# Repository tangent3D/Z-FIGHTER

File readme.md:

### Description
Z-FIGHTER is a Z80 hobby computer loosely based on [Grant Searle's CP/M on breadboard](http://searle.x10host.com/cpm/index.html "Grant Searle's CP/M on breadboard") project. As a fully assembled unit in its custom 3D-printed enclosure, Z-FIGHTER has a handheld-style form factor with front panel accessories intended for user-created software and games. Connected via serial to a computer or terminal, Z-FIGHTER can be used to enjoy a full CP/M 2.2 environment or Microsoft BASIC in ROM. Finally, a parallel port and external CPU control pins are provided to the user for hardware hacking and expansion.

### Specifications
- Z80 CPU @ 7.3728MHz
- CompactFlash interface for CP/M 2.2 operating system and file storage
- Z80 SIO/0 with dual 115200 bps RS-232 ports
- Jumper-selectable optional clock oscillator (X2) for SIO/0 port B (e.g.  614.4 KHz/64 for 9600 bps)
- Jumper-selectable RS-232 CTS flow control
- i8255 PPI-based parallel port reserved for front panel accessory daughterboard
- i8255 PPI-based user parallel port
- 512K ROM with external DIP-3 switches for manual ROM paging and ATF22V10C SPLD for memory map customization
- USB type-B power connector
- DS1233 supervisory circuit
- Optional jumpers to supply +5V to pin 9 on RS-232 ports (non-standard, for use at user's own risk)
- External CPU control header exposing #INT, #NMI, #WAIT, #RESET, system clock and SIO Ch. B clock signals

### Accessory board specifications
- 8x Cherry MX key switches
- ST7920 128x64 LCD module with software-controllable backlight
- Electromagnetic buzzer (CPU-controlled)

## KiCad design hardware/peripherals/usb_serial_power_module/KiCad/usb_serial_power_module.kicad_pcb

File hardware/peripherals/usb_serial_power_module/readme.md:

USB serial adapter with software-controllable pin 9 +5V. Not adherent to RS-232 standard. For use with Z-FIGHTER only.

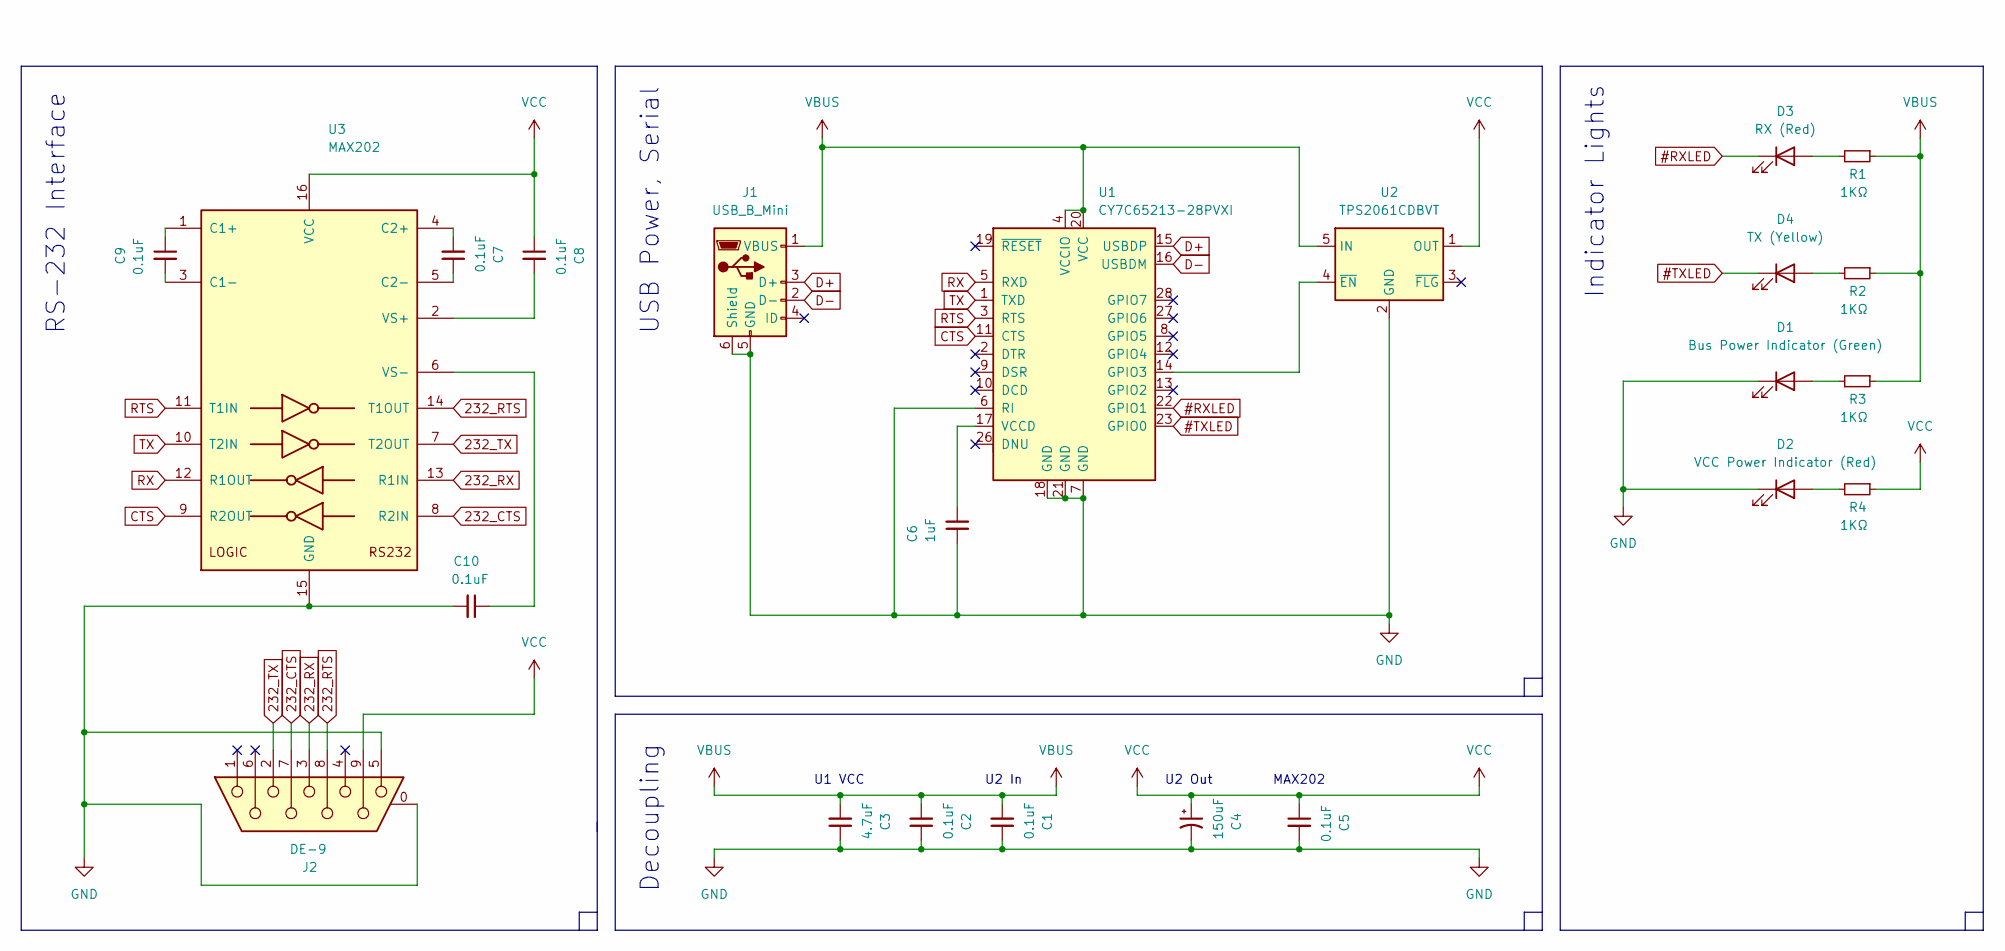
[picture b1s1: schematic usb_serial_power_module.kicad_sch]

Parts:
C1, C2, C5, C7, C8, C9, C10: 0.1uF; C_0805_2012Metric_Pad1.18x1.45mm_HandSolder
C3: 4.7uF; C_0805_2012Metric_Pad1.18x1.45mm_HandSolder
C4: 150uF; CP_EIA-6032-15_Kemet-U_Pad2.25x2.35mm_HandSolder
C6: 1uF; C_0805_2012Metric_Pad1.18x1.45mm_HandSolder
D1: Bus Power Indicator (Green); LED_0805_2012Metric_Pad1.15x1.40mm_HandSolder
D2: VCC Power Indicator (Red); LED_0805_2012Metric_Pad1.15x1.40mm_HandSolder
D3: RX (Red); LED_0805_2012Metric_Pad1.15x1.40mm_HandSolder
D4: TX (Yellow); LED_0805_2012Metric_Pad1.15x1.40mm_HandSolder
J1: USB_B_Mini; USB_Mini-B_Wuerth_65100516121_Horizontal
J2: DE-9; DSUB-9_Female_Horizontal_P2.77x2.84mm_EdgePinOffset7.70mm_H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
R1, R2, R3, R4: 1KΩ; R_0805_2012Metric_Pad1.20x1.40mm_HandSolder
U1: CY7C65213-28PVXI; SSOP-28_5.3x10.2mm_P0.65mm
U2: TPS2061CDBVT; SOT-23-5
U3: MAX202; SOIC-16_3.9x9.9mm_P1.27mm

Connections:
232_CTS: J2.7, U3.8 (R2IN)
232_RTS: J2.8, U3.14 (T1OUT)
232_RX: J2.3, U3.13 (R1IN)
232_TX: J2.2, U3.7 (T2OUT)
#RXLED: D3.1 (K), U1.22 (GPIO1)
#TXLED: D4.1 (K), U1.23 (GPIO0)
CTS: U1.11 (CTS), U3.9 (R2OUT)
D+: J1.3 (D+), U1.15 (USBDP)
D-: J1.2 (D-), U1.16 (USBDM)
GND: C1.1, C2.1, C3.1, C4.2, C5.2, C6.1, C10.2, D1.1 (K), D2.1 (K), J1.5 (GND), J1.6 (Shield), J2.0 (PAD), J2.5, U1.6 (RI), U1.7 (GND), U1.18 (GND), U1.21 (GND), U2.2 (GND), U3.15 (GND)
unnamed: C6.2, U1.17 (VCCD)
unnamed: C7.1, U3.5 (C2-)
unnamed: C7.2, U3.4 (C2+)
unnamed: C8.2, U3.2 (VS+)
unnamed: C9.1, U3.1 (C1+)
unnamed: C9.2, U3.3 (C1-)
unnamed: C10.1, U3.6 (VS-)
unnamed: D3.2 (A), R1.2
unnamed: D4.2 (A), R2.2
unnamed: D1.2 (A), R3.2
unnamed: D2.2 (A), R4.2
unnamed: U1.14 (GPIO3), U2.4 (~EN)
RTS: U1.3 (RTS), U3.11 (T1IN)
RX: U1.5 (RXD), U3.12 (R1OUT)
TX: U1.1 (TXD), U3.10 (T2IN)
VBUS: C1.2, C2.2, C3.2, J1.1 (VBUS), R1.1, R2.1, R3.1, U1.4 (VCCIO), U1.20 (VCC), U2.5 (IN)
VCC: C4.1, C5.1, C8.1, J2.9, R4.1, U2.1 (OUT), U3.16 (VCC)

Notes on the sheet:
Indicator Lights
Decoupling
RS-232 Interface
U1 VCC
U2 In
USB Power, Serial
MAX202
U2 Out

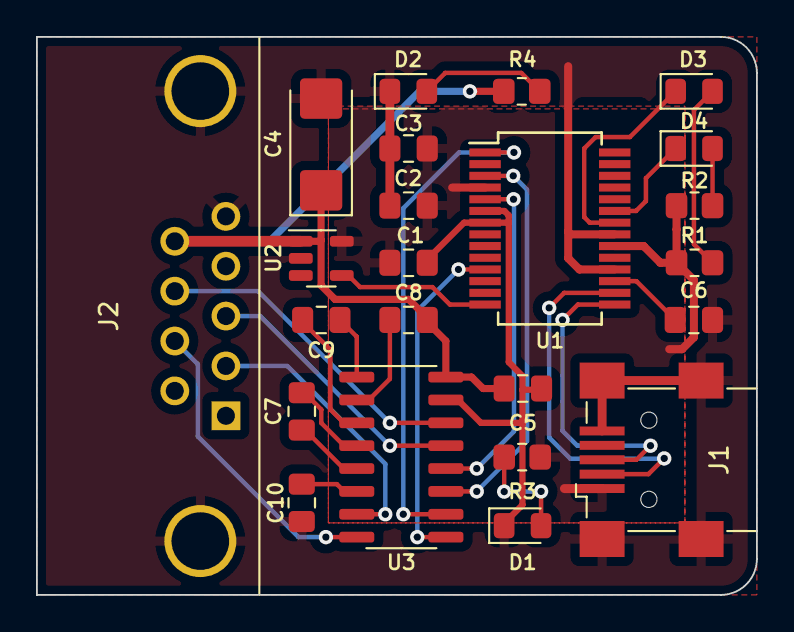
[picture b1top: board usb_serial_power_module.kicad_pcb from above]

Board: 2 copper layers, 40.0 x 31.0 mm, 23 parts (0 on the bottom side), 27 nets.

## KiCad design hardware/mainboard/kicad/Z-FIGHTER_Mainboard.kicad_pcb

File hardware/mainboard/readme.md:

## Z-FIGHTER Mainboard

[PCB schematic](../../media/schematic_mainboard.pdf)

[PCB layout](../../media/layout_mainboard.pdf)

## Bill of Materials
|Part Description|Quantity|Mouser #|Link
|--|--|--|--|
Z84C0008PEG Z80 CPU|1|692-Z84C0008PEG|[Mouser](https://www.mouser.com/ProductDetail/?qs=1C6%2FyOstnVvOWPsPt2TcAQ%3D%3D)
AS6C4008-55PCN 512K x8 SRAM|1|913-AS6C4008-55PCN|[Mouser](https://www.mouser.com/ProductDetail/?qs=E5c5%252Bmu3i3%252BMOyro1Tlhzg%3D%3D)
SST39SF040-70-4C-PHE 512K x8 EEPROM|1|804-39SF0407CPHE|[Mouser](https://www.mouser.com/ProductDetail/?qs=YClUa%252B2dcx1pgizrqJ6nyQ%3D%3D)
82C55A Programmable Peripheral Interface|2||[Jameco](https://www.jameco.com/z/82C55A-Major-Brands-IC-82C55A-CPU-PERIPHERAL-INTERFACE-8MHZ-DIP-40-pin_52417.html)
MAX203EPP +5V RS-232 Transceiver|2|700-MAX203EPPG36|[Mouser](https://www.mouser.com/ProductDetail/?qs=CDqwynd4ZNogpJr0Fmpb1w%3D%3D)
USB 2.0 RA Receptacle Type B|1|530-SS-52300-001|[Mouser](https://www.mouser.com/ProductDetail/?qs=gZXFycFWdAM098VuPZGg2w%3D%3D)
Resistor Network 10K 4Pin Bussed|1|652-4604X-1LF-10K|[Mouser](https://www.mouser.com/ProductDetail/?qs=jXOqZ2xt48NO%2FqYoJux7tg%3D%3D)
DE-9 R/A male connector|2|806-K22X-E9P-N-99|[Mouser](https://www.mouser.com/ProductDetail/?qs=SY6bF4iPirTJ1N%2FB520%252B5Q%3D%3D)
Resistor Network 1K 4Pin Bussed|1|652-4604X-1LF-1K|[Mouser](https://www.mouser.com/ProductDetail/?qs=xtl3rb8zXsvZ4tyOouOFIw%3D%3D)
Ceramic Disc Capacitor 100pF|1|594-D101K20Y5PL63L6R|[Mouser](https://www.mouser.com/ProductDetail/?qs=GtWgGqLahXfZ4CSgyYo67w%3D%3D)
40P 2R male vertical box header|1|538-70246-4004|[Mouser](https://www.mouser.com/ProductDetail/?qs=g5f4E6w8l8h7b35ebEIf2w%3D%3D)
Tactile Switches R/A 6X6 6.15mm BTN|1|653-B3F-3152|[Mouser](https://www.mouser.com/ProductDetail/?qs=Pjd0UV7BHP%252BLeRBK3ENKog%3D%3D)
Socket OSCILLATOR FULL 4PIN|2|535-1107741|[Mouser](https://www.mouser.com/ProductDetail/?qs=WZRMhwwaLl%2FApwqojhfzdA%3D%3D)
ATF22V10C EEPLD|1|556-AF22V10C15PU|[Mouser](https://www.mouser.com/ProductDetail/?qs=2mdvTlUeTfCr46ZvfjTtAg%3D%3D)
Supervisory Circuits 5V EconoReset|1|700-DS1233-5|[Mouser](https://www.mouser.com/ProductDetail/?qs=0Y9aZN%252BMVCWOcj0LQZHuFQ%3D%3D)
Standard Clock Oscillators DIP-14 5V 7.3728MHz|1|520-TCF737-X|[Mouser](https://www.mouser.com/ProductDetail/?qs=GxOUx7aO6nw6OhbIEx8owA%3D%3D)
SN74HC00|1|595-SN74HC00AN|[Mouser](https://www.mouser.com/ProductDetail/?qs=6ZVwTuetbD7YqMbSpl34ug%3D%3D)
Z84C4010PEG Z80 SIO/0|1|692-Z84C4010PEG|[Mouser](https://www.mouser.com/ProductDetail/?qs=ZNtr8jqNHF4vszdb5PeVGw%3D%3D)
.100 Shunt|4|200-SNT100BKGH|[Mouser](https://www.mouser.com/ProductDetail/?qs=92ilVni64gz8scrxywNMxw%3D%3D)
3 POS DIP switch R/A|1|490-DS02C-254-1L03BE|[Mouser](https://www.mouser.com/ProductDetail/?qs=wnTfsH77Xs4jkggh8giIBw%3D%3D)
Headers & Wire Housings 26P R/A|1|517-30326-5002|[Mouser](https://www.mouser.com/ProductDetail/?qs=QV10cN0MjFuwK57KknWtBg%3D%3D)
10uF radial electrolytic capacitor|1|667-ECA-1EM100I|[Mouser](https://www.mouser.com/ProductDetail/?qs=rMMd5vBiahoPyQAc8NWEpA%3D%3D)
Socket 40P DIP|4|649-DILB40P223TLF|[Mouser](https://www.mouser.com/ProductDetail/?qs=dNsYR%2FH0PyPZ7Cx3x%252BXI2w%3D%3D)
Socket 32P DIP|2|649-DILB32P223TLF|[Mouser](https://www.mouser.com/ProductDetail/?qs=dNsYR%2FH0PyPAfvGxulPprw%3D%3D)
Socket 20P DIP|2|517-4820-3004-CP|[Mouser](https://www.mouser.com/ProductDetail/?qs=IGgAdOvCTsThtp8UbkGeUw%3D%3D)
Socket 14P DIP|1|517-4814-3000-CP|[Mouser](https://www.mouser.com/ProductDetail/?qs=IGgAdOvCTsSwgxfUvPVZeg%3D%3D)
Socket 24P DIP|1|649-DILB24P-224TLF|[Mouser](https://www.mouser.com/ProductDetail/?qs=cTNRJjk9LRekdjb2T7GbOg%3D%3D)
Ceramic capacitor 0.1uF 50V 5mm|12|594-K104K15X7RF53H5|[Mouser](https://www.mouser.com/ProductDetail/?qs=sYfpZ29HcUSlgH5bSUHkYw%3D%3D)
Resistor Network 4.7K 4Pin Bussed|1|652-4604X-1LF-4.7K|[Mouser](https://www.mouser.com/ProductDetail/?qs=10P5Hhl%252BD79Zc7vt0%2Fhnuw%3D%3D)
26P 2R vertical female header|1|855-M20-7831346|[Mouser](https://www.mouser.com/ProductDetail/?qs=Jph8NoUxIfWtokGFIxN9SQ%3D%3D)
1x3P vertical pin header|4|649-68000-403H|[Mouser](https://www.mouser.com/ProductDetail/?qs=eanFghet1JNqC%2F0Iz%252BuUPw%3D%3D)
1x2P vertical pin header|2|649-68000-402HLF|[Mouser](https://www.mouser.com/ProductDetail/?qs=Jhn0v8ulSDtl9VR1zMrdxQ%3D%3D)
8P R/A male box header|1|710-61200821721|[Mouser](https://www.mouser.com/ProductDetail/?qs=PhR8RmCirEb56BXUsQNR%2FQ%3D%3D)
M3 standoff (20mm)|4||[Amazon](https://www.amazon.com/dp/B07PK23VC4/ref=cm_sw_r_tw_dp_NGRJ3TRHWGEE7J0RGDNS?_encoding=UTF8&psc=1)
M3 socket head cap screw|12||[Amazon](https://www.amazon.com/dp/B078V3YCF6/ref=cm_sw_r_tw_dp_TQ4HJWWVDEA1XZR15HDK?_encoding=UTF8&psc=1)
M3 nut|4||[Amazon](https://www.amazon.com/dp/B078V3YCF6/ref=cm_sw_r_tw_dp_TQ4HJWWVDEA1XZR15HDK?_encoding=UTF8&psc=1)
(Optional) M3 rubber feet (D12 x 10 x H7mm)|4||[Amazon](https://www.amazon.com/dp/B07LF1J7ZB/ref=cm_sw_r_tw_dp_JDTK9C1A8TC8FPBZZV7F?_encoding=UTF8&psc=1)

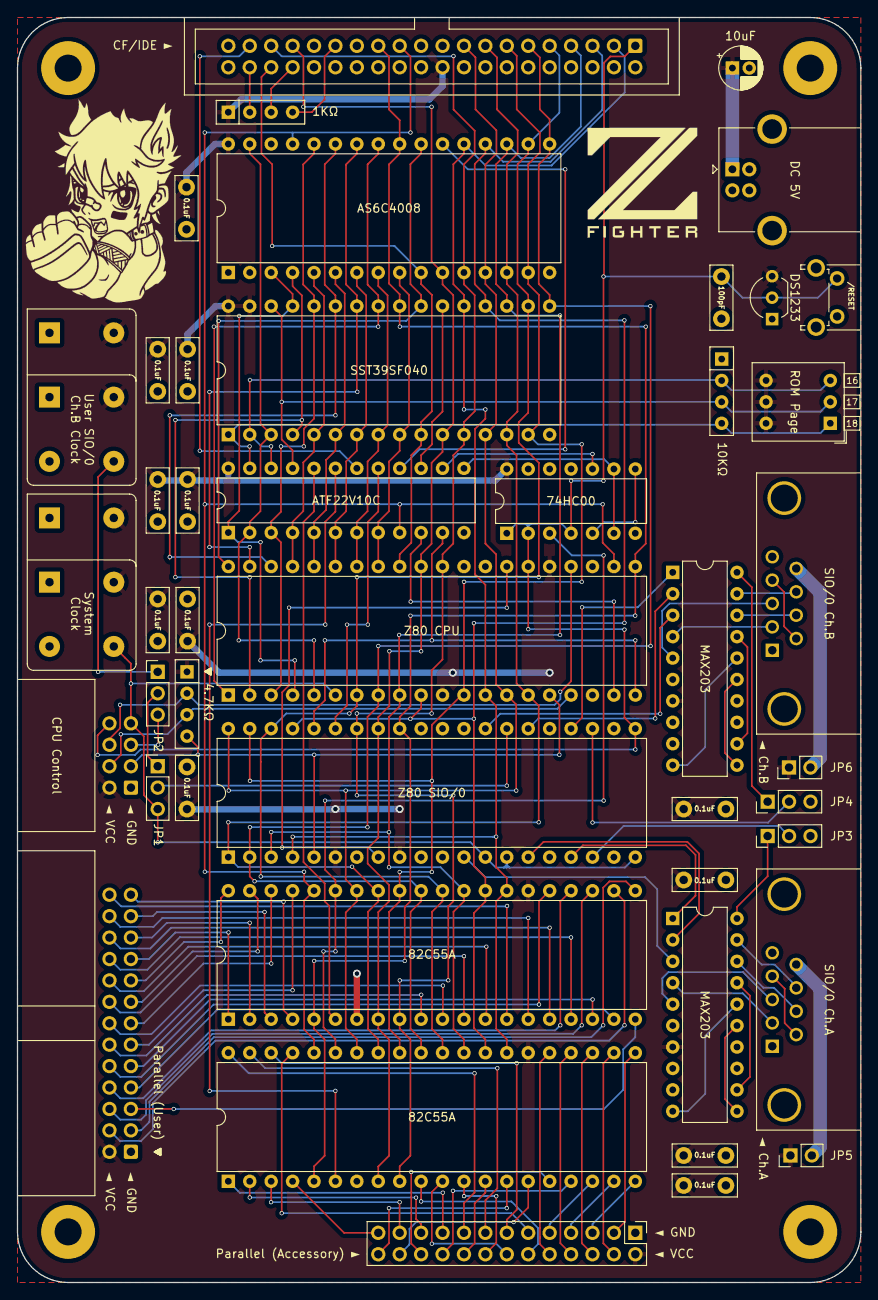
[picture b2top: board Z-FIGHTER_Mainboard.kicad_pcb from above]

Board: 2 copper layers, 100.0 x 150.0 mm, 49 parts (0 on the bottom side), 132 nets.

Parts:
C1: 10uF; CP_Radial_D5.0mm_P2.00mm
C2: 100pF; C_Disc_D7.5mm_W2.5mm_P5.00mm
C3, C4, C5, C6, C7, C8, C9, C10, C11, C12, C13, C14: 0.1uF; C_Disc_D7.5mm_W2.5mm_P5.00mm
IC1: Z80SIO; DIP-40_W15.24mm
J1, J2: DB9_Male_MountingHoles; DSUB-9_Male_Horizontal_P2.77x2.84mm_EdgePinOffset7.70mm_Hou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
J3: USB_B; USB_B_OST_USB-B1HSxx_Horizontal
J4: Conn_02x13_Odd_Even; PinHeader_2x13_P2.54mm_Vertical
J5: Conn_Parallel_User; IDC-Header_2x13_P2.54mm_Horizontal
J6: Conn_PATA; IDC-Header_2x20_P2.54mm_Vertical
J7: Conn_02x04_Odd_Even; IDC-Header_2x04_P2.54mm_Horizontal
JP1, JP2, JP3, JP4: Jumper_3_Open; PinHeader_1x03_P2.54mm_Vertical
JP5, JP6: Jumper_2_Open; PinHeader_1x02_P2.54mm_Vertical
Mount1, Mount2, Mount3, Mount4: MountingHole_3.2mm_M3_Pad
RN1: 4.7KΩ; R_Array_SIP4
RN2: 10KΩ; R_Array_SIP4
RN3: 1KΩ; R_Array_SIP4
SW1: SW_Push; SW_Tactile_SPST_Angled_PTS645Vx58-2LFS
SW2: SW_DIP_x03; SW_DIP_SPSTx03_Piano_10.8x9.18mm_W7.62mm_P2.54mm
U1: AS6C4008-55PCN; DIP-32_W15.24mm
U2: Z80CPU; DIP-40_W15.24mm
U3, U9: 82C55A; DIP-40_W15.24mm
U4: SST39SF040; DIP-32_W15.24mm
U5, U6: MAX203; DIP-20_W7.62mm
U7: ATF22V10CZ-15PI; DIP-24_W7.62mm
U8: 74HC00; DIP-14_W7.62mm
U10: DS1233; TO-92_Inline_Wide
X1: Z80/SIO Ch.A Clock; Oscillator_DIP-14_LargePads
X2: SIO Ch.B Clock; Oscillator_DIP-14_LargePads

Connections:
#CFCS: J6.37, U7.18
#INT: IC1.5, J7.3, RN1.4, U2.16
#IORQ: IC1.36, U2.20, U7.11
#M1: IC1.8, U2.27
#MREQ: U2.19, U7.10
#NMI: J7.4, RN1.3, U2.17
#PPIS_CS: U3.6, U7.19
#PPIU_CS: U7.20, U9.6
#RAMCS: U1.22, U7.16
#RD: IC1.32, J6.25, U1.24, U2.21, U3.5, U4.24, U9.5
#RESET: C2.2, IC1.21, J6.1, J7.8, SW1.1, U2.26, U8.1, U8.2, U8.4, U10.2
#ROMCS: U4.22, U7.15
#ROMD_IN: U7.13, U8.6, U8.9
#ROMD_OUT: U7.14, U8.10
#SIOCS: IC1.35, U7.17
#WAIT: J7.6, RN1.2, U2.24
#WR: J6.23, U1.29, U2.22, U3.36, U7.9, U9.36
A0: IC1.34, J6.35, U1.12, U2.30, U3.9, U4.12, U9.9
A1: IC1.33, J6.33, U1.11, U2.31, U3.8, U4.11, U9.8
A2: J6.36, U1.10, U2.32, U4.10
A3: U1.9, U2.33, U4.9, U7.8
A4: U1.8, U2.34, U4.8, U7.7
A5: U1.7, U2.35, U4.7, U7.6
A6: U1.6, U2.36, U4.6, U7.5
A7: U1.5, U2.37, U4.5, U7.4
A8: U1.27, U2.38, U4.27
A9: U1.26, U2.39, U4.26
A10: U1.23, U2.40, U4.23
A11: U1.25, U2.1, U4.25
A12: U1.4, U2.2, U4.4
A13: U1.28, U2.3, U4.28, U7.3
A14: U1.3, U2.4, U4.29, U7.1
A15: U1.31, U2.5, U4.3, U7.2
CLOCK: IC1.13, IC1.14, IC1.20, J7.7, JP1.3, U2.6, X1.8
CLOCK2: JP2.1, X2.8
CLOCK2_EXT: J7.5, JP2.3
CLOCK2_USER: JP1.1, JP2.2
CLOCK_Ch.B: IC1.27, JP1.2
CTSA: JP3.1, U5.20
CTSB: JP4.1, U6.20
D0: IC1.40, J6.17, U1.13, U2.14, U3.34, U4.13, U9.34
D1: IC1.1, J6.15, U1.14, U2.15, U3.33, U4.14, U9.33
D2: IC1.39, J6.13, U1.15, U2.12, U3.32, U4.15, U9.32
D3: IC1.2, J6.11, U1.17, U2.8, U3.31, U4.17, U9.31
D4: IC1.38, J6.9, U1.18, U2.7, U3.30, U4.18, U9.30
D5: IC1.3, J6.7, U1.19, U2.9, U3.29, U4.19, U9.29
D6: IC1.37, J6.5, U1.20, U2.10, U3.28, U4.20, U9.28
D7: IC1.4, J6.3, U1.21, U2.13, U3.27, U4.21, U9.27
GND: C1.2, C2.1, C3.2, C4.2, C5.2, C6.2, C7.2, C8.2, C9.2, C10.2, C11.2, C12.2, C13.1, C14.2, IC1.19, IC1.22, IC1.31, J1.0, J1.5, J2.0, J2.5, J3.4, J3.5, J4.1, J5.1, J6.2, J6.19, J6.22, J6.24, J6.26, J6.30, J6.40, J7.1, JP3.3, JP4.3, RN2.1, SW1.2, U1.1, U1.2, U1.16, U1.30, U2.29, U3.7, U4.16, U5.6, U5.9, U6.6, U6.9, U7.12, U8.7, U8.12, U8.13, U9.7, U10.1, X1.7, X2.7
unnamed: J1.4, J1.6
unnamed: J1.9, JP5.2
unnamed: J2.4, J2.6
unnamed: J2.9, JP6.2
unnamed: U5.10, U5.16
unnamed: U5.11, U5.15
unnamed: U5.12, U5.17
unnamed: U6.10, U6.16
unnamed: U6.11, U6.15
unnamed: U6.12, U6.17
unnamed: U8.5, U8.8
PA0S: J4.25, U3.4
PA0U: J5.25, U9.4
PA1S: J4.23, U3.3
PA1U: J5.23, U9.3
PA2S: J4.21, U3.2
PA2U: J5.21, U9.2
PA3S: J4.19, U3.1
PA3U: J5.19, U9.1
PA4S: J4.17, U3.40
PA4U: J5.17, U9.40
PA5S: J4.15, U3.39
PA5U: J5.15, U9.39
PA6S: J4.13, U3.38
PA6U: J5.13, U9.38
PA7S: J4.11, U3.37
PA7U: J5.11, U9.37
PATA29: J6.29, RN3.4
PATA34: J6.34, RN3.3
PATA38: J6.38, RN3.2
PB0S: J4.9, U3.18
PB0U: J5.9, U9.18
PB1S: J4.7, U3.19
PB1U: J5.7, U9.19
PB2S: J4.5, U3.20
PB2U: J5.5, U9.20
PB3S: J4.3, U3.21
PB3U: J5.3, U9.21
PB4S: J4.4, U3.22
PB4U: J5.4, U9.22
PB5S: J4.6, U3.23
PB5U: J5.6, U9.23
PB6S: J4.8, U3.24
PB6U: J5.8, U9.24
PB7S: J4.10, U3.25
PB7U: J5.10, U9.25
PC0S: J4.26, U3.14
PC0U: J5.26, U9.14
PC1S: J4.24, U3.15
PC1U: J5.24, U9.15
PC2S: J4.22, U3.16
PC2U: J5.22, U9.16
PC3S: J4.20, U3.17
PC3U: J5.20, U9.17
PC4S: J4.18, U3.13
PC4U: J5.18, U9.13
PC5S: J4.16, U3.12
PC5U: J5.16, U9.12
PC6S: J4.14, U3.11
PC6U: J5.14, U9.11
PC7S: J4.12, U3.10
PC7U: J5.12, U9.10
RESET: U3.35, U8.3, U9.35
ROMA16: RN2.2, SW2.3, U4.2, U7.22
ROMA17: RN2.3, SW2.2, U4.30, U7.21
ROMA18: RN2.4, SW2.1, U4.1, U7.23
RTSA: IC1.17, U5.1
RTSB: IC1.24, U6.1
RXDA: IC1.12, U5.3
RXDB: IC1.28, U6.3
S1CTS: J1.8, U5.19
S1RTS: J1.7, U5.18
S1RX: J1.2, U5.4
S1TX: J1.3, U5.5
S2CTS: J2.8, U6.19
S2RTS: J2.7, U6.18
S2RX: J2.2, U6.4
S2TX: J2.3, U6.5
SIO_CTSA: IC1.18, JP3.2
SIO_CTSB: IC1.23, JP4.2
TXDA: IC1.15, U5.2
TXDB: IC1.26, U6.2
VCC: C1.1, C3.1, C4.1, C5.1, C6.1, C7.1, C8.1, C9.1, C10.1, C11.1, C12.1, C13.2, C14.1, IC1.6, IC1.9, J3.1, J4.2, J5.2, J6.20, J7.2, JP5.1, JP6.1, RN1.1, RN3.1, SW2.4, SW2.5, SW2.6, U1.32, U2.11, U2.25, U3.26, U4.31, U4.32, U5.7, U6.7, U7.24, U8.14, U9.26, U10.3, X1.14, X2.14

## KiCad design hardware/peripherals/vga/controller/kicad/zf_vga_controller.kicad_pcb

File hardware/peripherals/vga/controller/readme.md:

## Z-FIGHTER VGA Controller

[Project Notes](https://tangent.space/vga.htm)

[PCB schematic](../../../../media/schematic_vga_controller.pdf)

[PCB layout (Front)](../../../../media/layout_vga_controller_front.pdf)

[PCB layout (Back)](../../../../media/layout_vga_controller_back.pdf)

## Bill of Materials
|Reference|Description|Mouser #|Link
|--|--|--|--|
U1|74HC241||
R1,R2|Resistor, 1KΩ, 1/4W||
RN1,RN2|Resistor Array, Bussed, 10KΩ, 4x, SIP-5||
C1|Capacitor, 0.1uF, 5mm||
Q1|BC547, TO-92||
SW1 - SW8|Switch, Omron B3F-4050||
J1|DE-9, Female, R/A||

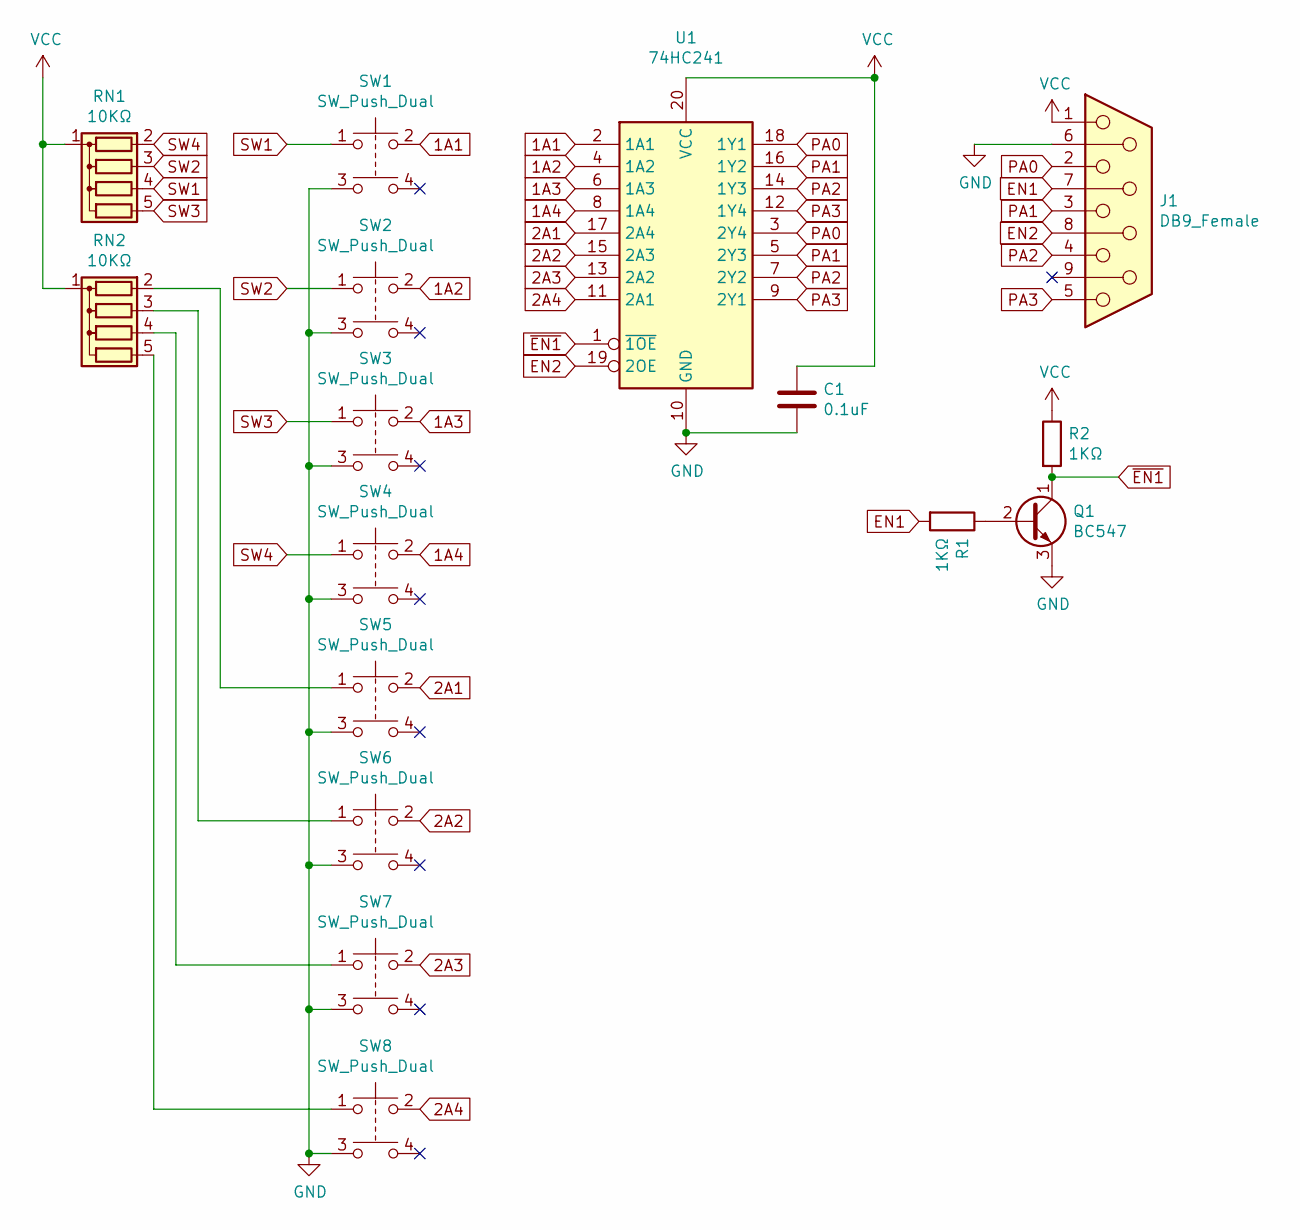
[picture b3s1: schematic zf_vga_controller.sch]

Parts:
C1: 0.1uF; C_Disc_D7.5mm_W2.5mm_P5.00mm
J1: DB9_Female; DSUB-9_Female_Horizontal_P2.77x2.84mm_EdgePinOffset7.70mm_H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
Q1: BC547; TO-92_Inline_Wide
R1, R2: 1KΩ; R_Axial_DIN0207_L6.3mm_D2.5mm_P7.62mm_Horizontal
RN1, RN2: 10KΩ; R_Array_SIP5
SW1, SW2, SW3, SW4, SW5, SW6, SW7, SW8: SW_Push_Dual; SW_B3F-4050
U1: 74HC241; DIP-20_W7.62mm

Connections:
1A1: SW1.2, U1.2 (1A1)
1A2: SW2.2, U1.4 (1A2)
1A3: SW3.2, U1.6 (1A3)
1A4: SW4.2, U1.8 (1A4)
2A1: SW5.2, U1.17 (2A4)
2A2: SW6.2, U1.15 (2A3)
2A3: SW7.2, U1.13 (2A2)
2A4: SW8.2, U1.11 (2A1)
EN1: J1.7, R1.2
EN2: J1.8, U1.19 (2OE)
GND: C1.2, J1.6, Q1.3 (E), SW1.3, SW2.3, SW3.3, SW4.3, SW5.3, SW6.3, SW7.3, SW8.3, U1.10 (GND)
unnamed: Q1.2 (B), R1.1
unnamed: RN2.2 (R1), SW5.1
unnamed: RN2.3 (R2), SW6.1
unnamed: RN2.4 (R3), SW7.1
unnamed: RN2.5 (R4), SW8.1
PA0: J1.2, U1.3 (2Y4), U1.18 (1Y1)
PA1: J1.3, U1.5 (2Y3), U1.16 (1Y2)
PA2: J1.4, U1.7 (2Y2), U1.14 (1Y3)
PA3: J1.5, U1.9 (2Y1), U1.12 (1Y4)
SW1: RN1.4 (R3), SW1.1
SW2: RN1.3 (R2), SW2.1
SW3: RN1.5 (R4), SW3.1
SW4: RN1.2 (R1), SW4.1
VCC: C1.1, J1.1, R2.1, RN1.1 (common), RN2.1 (common), U1.20 (VCC)
~EN1: Q1.1 (C), R2.2, U1.1 (~1OE)

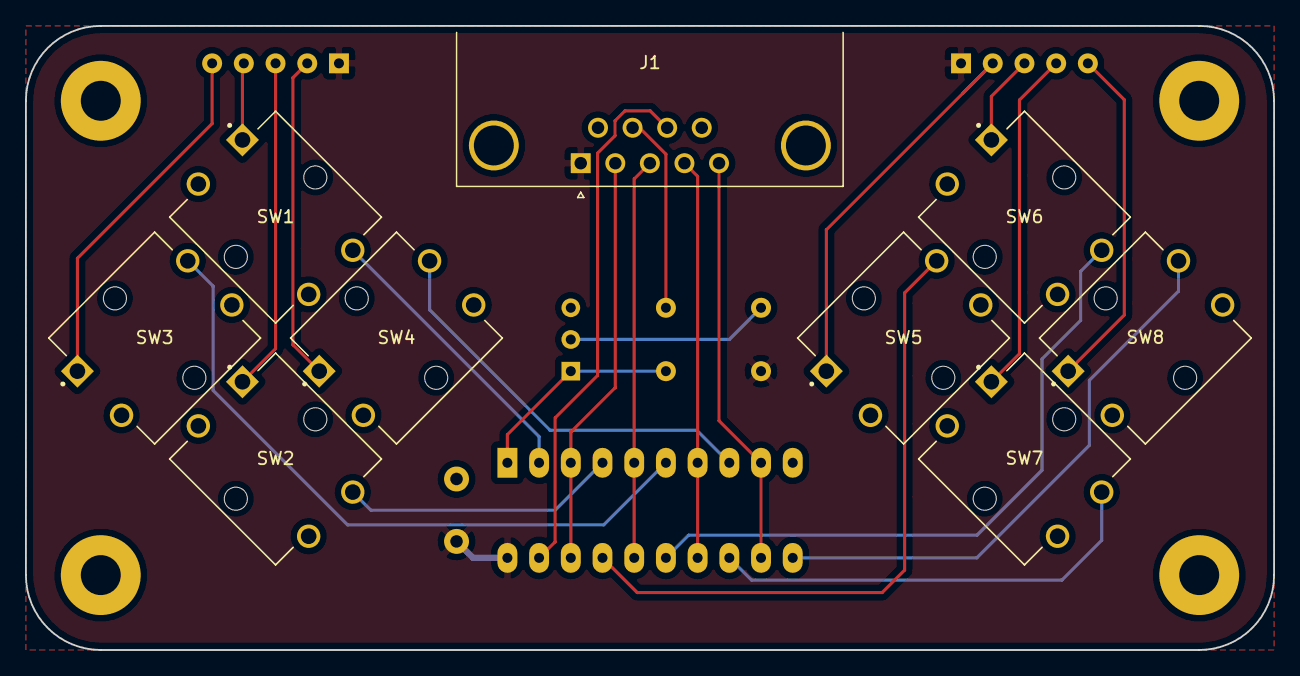
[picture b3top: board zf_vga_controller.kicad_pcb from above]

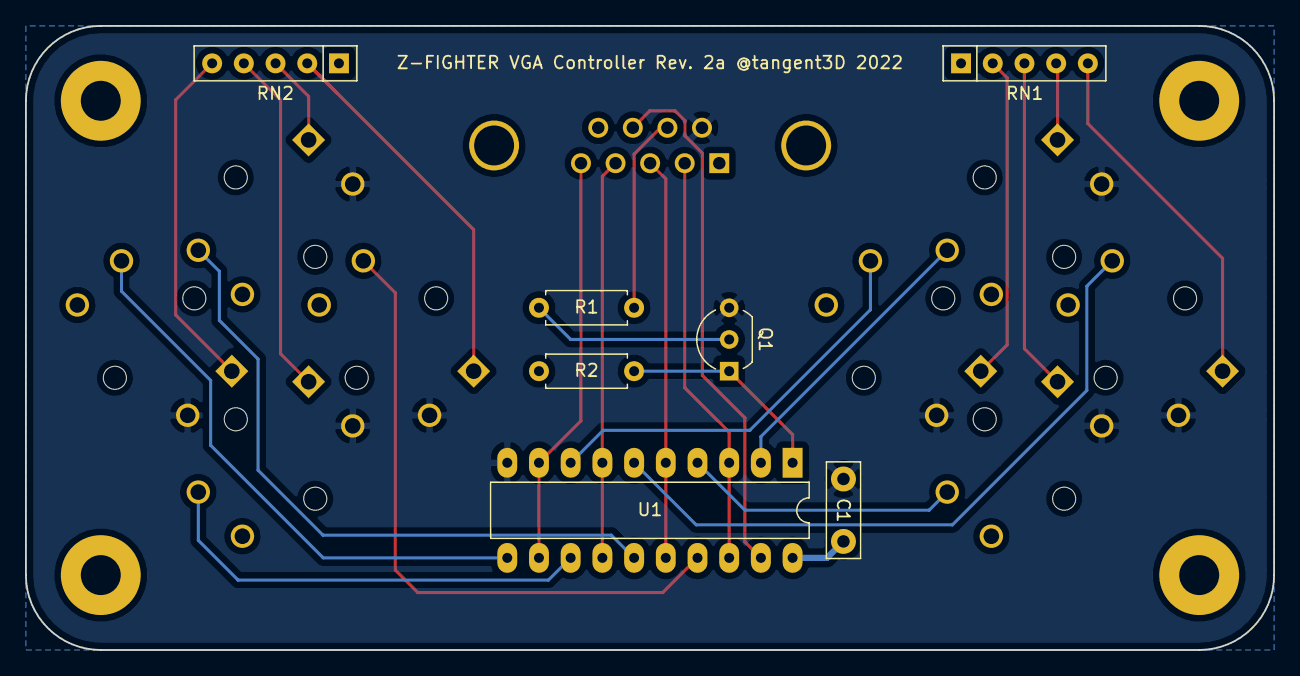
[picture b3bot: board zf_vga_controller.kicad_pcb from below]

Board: 2 copper layers, 100.0 x 50.0 mm, 20 parts (7 on the bottom side), 26 nets.

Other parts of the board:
Mount1, Mount1#2, Mount1#3, Mount1#4: MountingHole_3.2mm_M3_Pad

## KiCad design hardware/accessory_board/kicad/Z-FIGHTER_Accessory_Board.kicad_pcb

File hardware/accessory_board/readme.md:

## Z-FIGHTER Front Panel Accessory Board

[PCB schematic](../../media/schematic_accessory_board.pdf)

[PCB layout](../../media/layout_accessory_board.pdf)

## Bill of Materials
|Part Description|Quantity|Mouser #|Link
|--|--|--|--|
|Cherry MX switches (PCB mount)|8|540-MX1A-G1NW|[Mouser](https://www.mouser.com/ProductDetail/?qs=F5EMLAvA7IAf8LDkSr80OA%3D%3D)
|Resistor Network 10K 9Pin Bussed|1|652-4609H-1LF-10K|[Mouser](https://www.mouser.com/ProductDetail/Bourns/4609H-101-103LF?qs=sGAEpiMZZMujMHSoaAZeGdkD0yBqu0zL)
|WT-1205 electromagnetic buzzer|1|539-PB1224PE-05Q|[Mouser](https://www.mouser.com/ProductDetail/?qs=yTNxYlKScpyeBlcw7zrVEw%3D%3D)
|1N5817 Schottky diode|1|511-1N5817|[Mouser](https://www.mouser.com/ProductDetail/?qs=JV7lzlMm3yKNnxZdh%252BSMnw%3D%3D)
|BC337 NPN transistor|2|512-BC33725TAR|[Mouser](https://www.mouser.com/ProductDetail/?qs=u2B728UsA6qKwH1IAisoWA%3D%3D)
|1/4W 820 Ohm 5% resistor|1|603-CFR-25JT-52-820R|[Mouser](https://www.mouser.com/ProductDetail/?qs=KUIzHt%2Fe91nf0zePCO9VQg%3D%3D)
|1/4W 680 Ohm 5% resistor|1|603-CFR-25JB-52-680R|[Mouser](https://www.mouser.com/ProductDetail/?qs=oypCK0zG327gSAdGYp%2FJTg%3D%3D)
|1x20 right angle header|1|649-1012937992002BLF|[Mouser](https://www.mouser.com/ProductDetail/?qs=0lQeLiL1qybxcF3pstck9w%3D%3D)
|ST7920 128x64 Graphic LCD|1||[BuyDisplay](https://www.buydisplay.com/3-3v-5v-graphic-display-128x64-serial-lcd-display-st7920)
|20mm vertical double row breakaway header|1||[Amazon](https://www.amazon.com/uxcell-Straight-Connector-Arduino-Prototype/dp/B07DJY3FRJ/ref=sr_1_5?keywords=20mm+header+pins&qid=1637700921&sr=8-5)
|Right-angle header (female)|1||[Amazon](https://www.amazon.com/Yohii-Female-Header-2-54mm-Connector/dp/B07P1R9CGT/ref=sr_1_4?keywords=right+angle+female+header&qid=1637701159&sr=8-4)
|DSA profile 2U keycap|2||[Pimp My Keyboard](https://pimpmykeyboard.com/dsa-2-space-pack-of-4/)
|DSA profile 1U keycap|6||[Pimp My Keyboard](https://pimpmykeyboard.com/dsa-1-space-pack-of-10/)
|Cherry PCB snap-in 2U stabilizer|2||[Amazon](https://www.amazon.com/dp/B085T8QZJC/ref=cm_sw_r_tw_dp_V3VNQRQ0CPQBPXNV3A6B?_encoding=UTF8&psc=1)

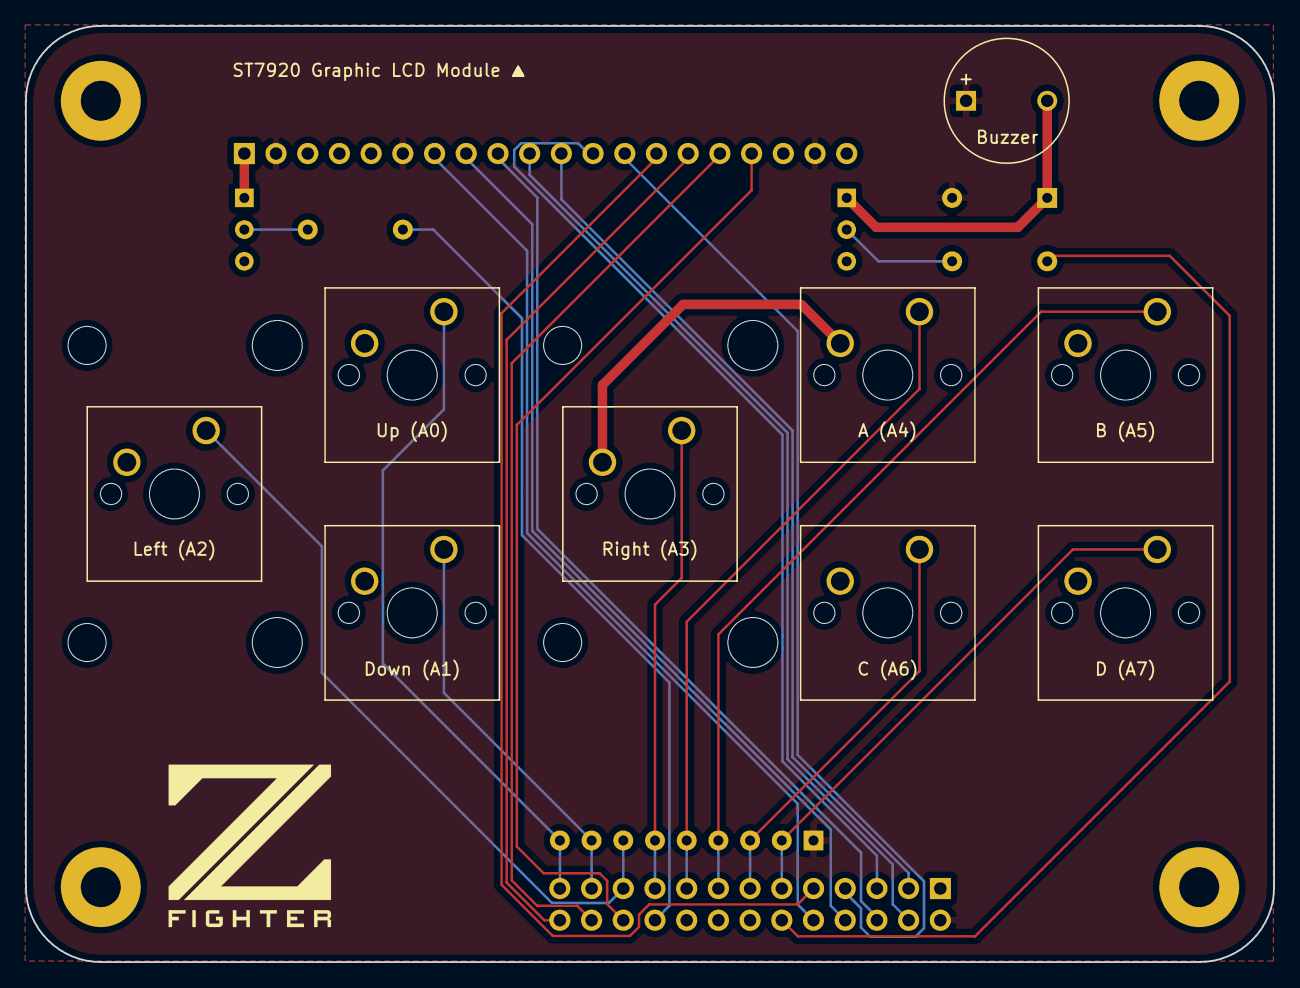
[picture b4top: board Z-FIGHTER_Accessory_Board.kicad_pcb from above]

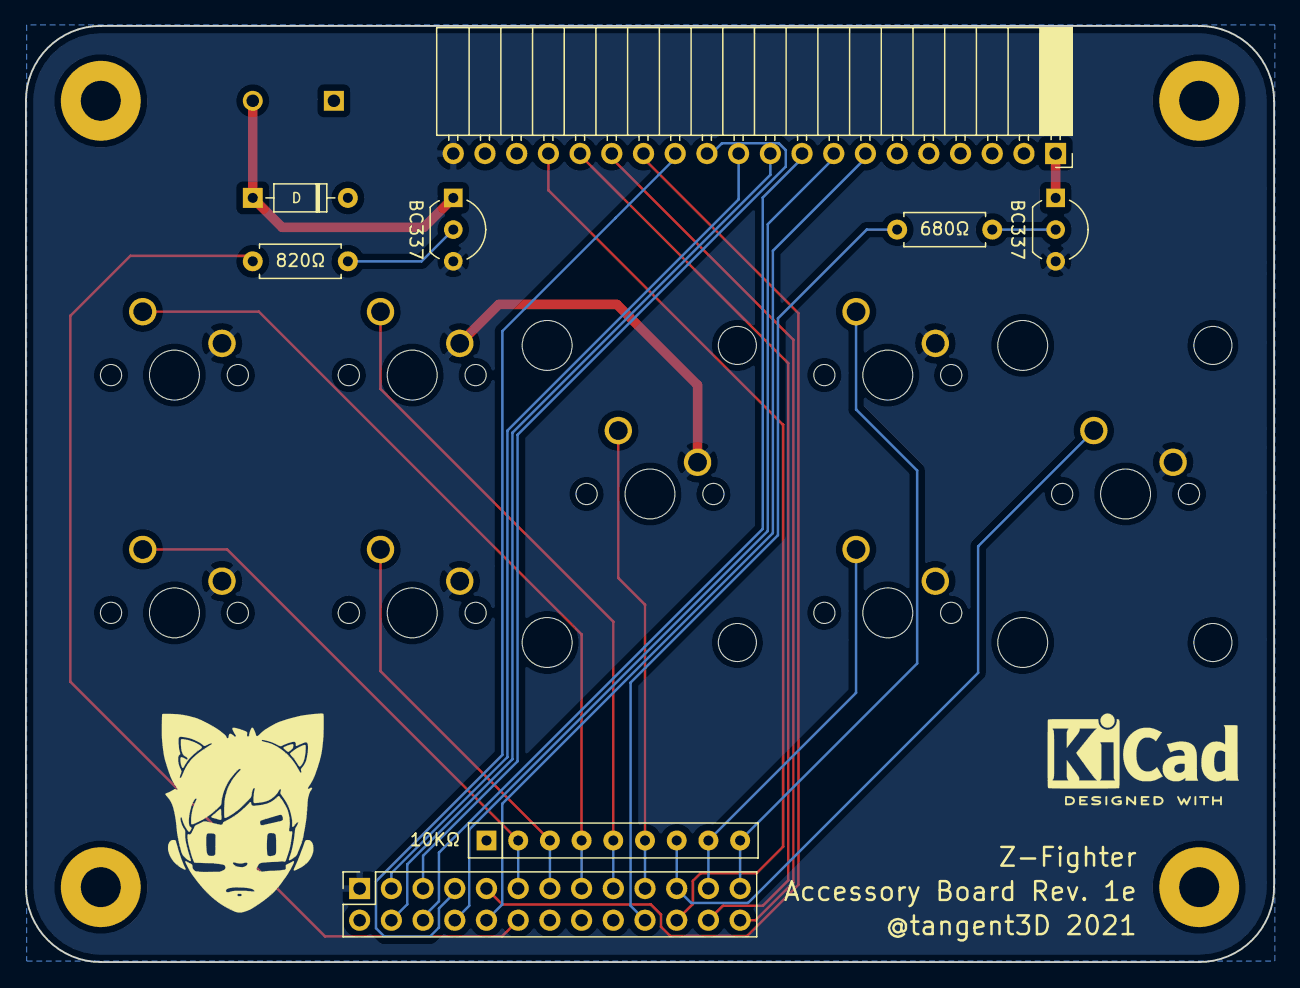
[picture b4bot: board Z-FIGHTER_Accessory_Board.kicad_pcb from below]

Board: 2 copper layers, 100.0 x 75.0 mm, 21 parts (8 on the bottom side), 27 nets.

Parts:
BZ1: Buzzer; MagneticBuzzer_ProSignal_ABT-410-RC
D2: IN5817; D_DO-35_SOD27_P7.62mm_Horizontal
J7: ST7920 Graphic LCD; PinSocket_1x20_P2.54mm_Horizontal
J9: Conn_02x13_Odd_Even; PinSocket_2x13_P2.54mm_Vertical
Mount1, Mount2, Mount3, Mount4: MountingHole_3.2mm_M3_Pad
Q1, Q2: BC337; TO-92_Inline_Wide
RB1: 680Ω; R_Axial_DIN0207_L6.3mm_D2.5mm_P7.62mm_Horizontal
RB2: 820Ω; R_Axial_DIN0207_L6.3mm_D2.5mm_P7.62mm_Horizontal
RN4: 10KΩ; R_Array_SIP9
SW1: Up (A0); SW_Cherry_MX_1.00u_PCB
SW2: Down (A1); SW_Cherry_MX_1.00u_PCB
SW3: Left (A2); SW_Cherry_MX_2.00u_Vertical_PCB
SW4: Right (A3); SW_Cherry_MX_2.00u_Vertical_PCB
SW5: A (A4); SW_Cherry_MX_1.00u_PCB
SW6: B (A5); SW_Cherry_MX_1.00u_PCB
SW7: C (A6); SW_Cherry_MX_1.00u_PCB
SW8: D (A7); SW_Cherry_MX_1.00u_PCB

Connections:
BLK: J7.1, Q1.1
GND: J7.20, J9.1, Q1.3, Q2.3, SW1.2, SW2.2, SW3.2, SW4.2, SW5.2, SW6.2, SW7.2, SW8.2
unnamed: BZ1.2, D2.1, Q2.1
unnamed: Q1.2, RB1.1
unnamed: Q2.2, RB2.1
PA0S: J9.25, RN4.9, SW1.1
PA1S: J9.23, RN4.8, SW2.1
PA2S: J9.21, RN4.7, SW3.1
PA3S: J9.19, RN4.6, SW4.1
PA4S: J9.17, RN4.5, SW5.1
PA5S: J9.15, RN4.4, SW6.1
PA6S: J9.13, RN4.3, SW7.1
PA7S: J9.11, RN4.2, SW8.1
PB0S: J7.14, J9.9
PB1S: J7.13, J9.7
PB2S: J7.12, J9.5
PB3S: J7.11, J9.3
PB4S: J7.10, J9.4
PB5S: J7.9, J9.6
PB6S: J7.8, J9.8
PB7S: J7.7, J9.10
PC0S: J7.15, J9.26
PC1S: J7.16, J9.24
PC2S: J7.17, J9.22
PC3S: J9.20, RB1.2
PC7S: J9.12, RB2.2
VCC: BZ1.1, D2.2, J7.2, J7.6, J7.19, J9.2, RN4.1

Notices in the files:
parts and their libraries:
Copyright 2021 Accelerated Designs. All rights reserved.
